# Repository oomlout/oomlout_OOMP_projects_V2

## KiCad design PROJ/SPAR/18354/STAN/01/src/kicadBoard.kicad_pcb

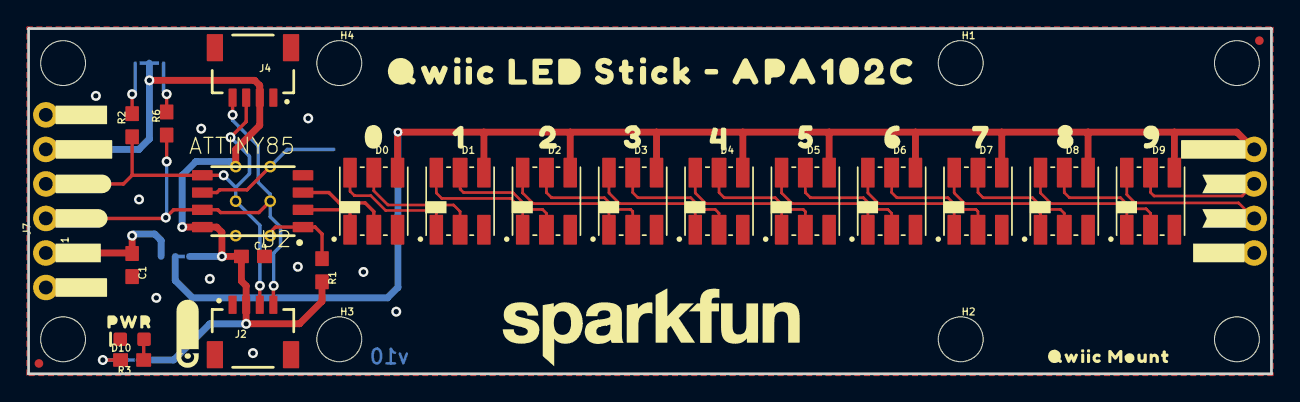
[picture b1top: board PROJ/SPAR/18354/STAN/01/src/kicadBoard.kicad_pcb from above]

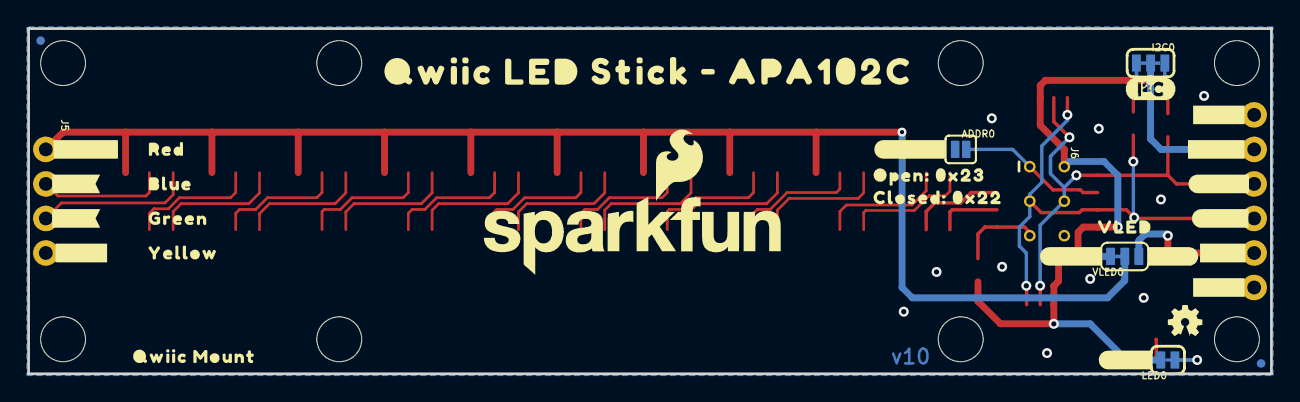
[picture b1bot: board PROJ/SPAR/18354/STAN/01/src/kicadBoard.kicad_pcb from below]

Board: 2 copper layers, 91.4 x 25.4 mm, 93 parts (35 on the bottom side), 34 nets.

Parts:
ADDR0: JUMPER-SMT_2_NO_SILK; SMT-JUMPER_2_NO_SILK
C1: 4.7uF; 0603
C4: 0.1uF; 0603
D0, D1, D2, D3, D4, D5, D6, D7, D8, D9: APA102-5050
D10: RED; LED-0603
FRAME1: FRAME-LETTER; CREATIVE_COMMONS
H1, H2, H3, H4: STAND-OFF
I2C0: JUMPER-SMT_3_2-NC_TRACE_SILK; SMT-JUMPER_3_2-NC_TRACE_SILK
J1: 1X02_NO_SILK
J2, J4: QWIIC_RA; JST04_1MM_RA
J5, J7: 1X04_NO_SILK
J6: AVR_SPI_PROG_3X2TESTPOINTS; 2X3_TEST_POINTS
JP1, JP2, JP5, JP6: FIDUCIALUFIDUCIAL; FIDUCIAL-MICRO
JP3, JP4, JP7, JP8: STAND-OFF
LED0: JUMPER-SMT_2_NC_TRACE_SILK; SMT-JUMPER_2_NC_TRACE_SILK
LOGO1: OSHW-LOGOMINI; OSHW-LOGO-MINI
LOGO2, LOGO5: SFE_LOGO_NAME.2_INCH; SFE_LOGO_NAME_.2
LOGO3: QWIIC_LOGO_5MM; QWIIC_5MM
LOGO4: SFE_LOGO_FLAME.2_INCH; SFE_LOGO_FLAME_.2
R1, R2, R6: 4.7k; 0603
R3: 1k; 0603
U2: ATTINY85
U$1, U$2, U$3, U$4, U$5, U$8: #GND#0
U$6: #CO#0
U$7: #DO#0
U$9, U$12: #VLED#0
U$10: #ADDR#0
U$11: (I_SUPER2_C)
U$14, U$17: #3#3V#0
U$15: #_DO#0
U$16: #_CO#0
U$18, U$19: #VIN#0
U$20: #SDA#0
U$21: #SDA_#0
U$22: #SCL#0
U$23: #SCL_#0
U$24: #LED#0
U$25: #3#3V#1
U$26: PWR0
U$28: VLED0
U$29: #VIN#4
U$30, U$47: QWIIC_MOUNT5
U$31: 00
U$32: 10
U$33: 20
U$34: 30
U$35: 40
U$36: 50
U$37: 60
U$38: 70
U$39: 80
U$40: 90
U$41: RED0
U$42: BLUE0
U$43: GREEN0
U$44: YELLOW0
U$45: OPEN#_0X230
U$46: CLOSED#_0X220
U$48, U$49: QWIIC_LED_STICK_#_APA102C0
VLED0: JUMPER-SMT_3_1-NC_TRACE_SILK; SMT-JUMPER_3_1-NC_TRACE_SILK

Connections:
3.3V: C4.1, I2C0.2, J2.2, J4.2, J6.2, J7.3, LED0.2, R1.2, U2.8, VLED0.3
ADDR/CIPO: ADDR0.2, J6.1, U2.6
CLK: D0.P2, U2.3
CO(10): D9.P5, J5.2
DO: D0.P1, U2.2
DO(10): D9.P6, J5.3
GND: ADDR0.1, C1.2, C4.2, D0.P3, D1.P3, D2.P3, D3.P3, D4.P3, D5.P3, D6.P3, D7.P3, D8.P3, D9.P3, D10.C, J1.2, J2.1, J4.1, J5.4, J6.6, J7.4, U2.4
unnamed: D10.A, R3.1
unnamed: LED0.1, R3.2
unnamed: I2C0.3, R2.2
unnamed: I2C0.1, R6.2
unnamed: D8.P6, D9.P1
unnamed: D8.P5, D9.P2
unnamed: D7.P5, D8.P2
unnamed: D7.P6, D8.P1
unnamed: D6.P5, D7.P2
unnamed: D6.P6, D7.P1
unnamed: D5.P5, D6.P2
unnamed: D5.P6, D6.P1
unnamed: D4.P5, D5.P2
unnamed: D4.P6, D5.P1
unnamed: D3.P5, D4.P2
unnamed: D3.P6, D4.P1
unnamed: D2.P6, D3.P1
unnamed: D2.P5, D3.P2
unnamed: D1.P6, D2.P1
unnamed: D1.P5, D2.P2
unnamed: D0.P5, D1.P2
unnamed: D0.P6, D1.P1
SCL/SCK: J2.4, J4.4, J6.3, J7.1, R6.1, U2.7
SDA/COPI: J2.3, J4.3, J6.4, J7.2, R2.1, U2.5
VIN: C1.1, J1.1, VLED0.1
VLED: D0.P4, D1.P4, D2.P4, D3.P4, D4.P4, D5.P4, D6.P4, D7.P4, D8.P4, D9.P4, J5.1, VLED0.2
~RST: J6.5, R1.1, U2.1

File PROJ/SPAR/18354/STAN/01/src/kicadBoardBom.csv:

"Id";"Designator";"Package";"Quantity";"Designation";"Supplier and ref";
1;"R2,R6,R1";"0603";3;"4.7k";;;
2;"U$3,U$1,U$5,U$4,U$8,U$2";"#GND#0";6;"";;;
3;"D3,D8,D4,D1,D2,D6,D0,D5,D9,D7";"APA102-5050";10;"APA102-5050";;;
4;"JP8,H3,JP3,H4,JP7,JP4,H1,H2";"STAND-OFF";8;"STAND-OFF";;;
5;"J1";"1X02_NO_SILK";1;"";;;
6;"U$35";"40";1;"";;;
7;"U$32";"10";1;"";;;
8;"JP6,JP2,JP1,JP5";"FIDUCIAL-MICRO";4;"FIDUCIALUFIDUCIAL";;;
9;"U$40";"90";1;"";;;
10;"U$38";"70";1;"";;;
11;"FRAME1";"CREATIVE_COMMONS";1;"FRAME-LETTER";;;
12;"U$37";"60";1;"";;;
13;"LOGO2,LOGO5";"SFE_LOGO_NAME_.2";2;"SFE_LOGO_NAME.2_INCH";;;
14;"D10";"LED-0603";1;"RED";;;
15;"J4,J2";"JST04_1MM_RA";2;"QWIIC_RA";;;
16;"U$9,U$12";"#VLED#0";2;"";;;
17;"U$36";"50";1;"";;;
18;"U$22";"#SCL#0";1;"";;;
19;"U$31";"00";1;"";;;
20;"U$48,U$49";"QWIIC_LED_STICK_#_APA102C0";2;"";;;
21;"U$26";"PWR0";1;"";;;
22;"U$7";"#DO#0";1;"";;;
23;"U$20";"#SDA#0";1;"";;;
24;"U$18,U$19";"#VIN#0";2;"";;;
25;"C1";"0603";1;"4.7uF";;;
26;"R3";"0603";1;"1k";;;
27;"U$6";"#CO#0";1;"";;;
28;"U$30,U$47";"QWIIC_MOUNT5";2;"";;;
29;"U2";"ATTINY85";1;"ATTINY85";;;
30;"U$34";"30";1;"";;;
31;"U$39";"80";1;"";;;
32;"LOGO3";"QWIIC_5MM";1;"QWIIC_LOGO_5MM";;;
33;"C4";"0603";1;"0.1uF";;;
34;"J7,J5";"1X04_NO_SILK";2;"";;;
35;"U$33";"20";1;"";;;
36;"U$14,U$17";"#3#3V#0";2;"";;;
37;"U$45";"OPEN#_0X230";1;"";;;
38;"U$46";"CLOSED#_0X220";1;"";;;
39;"U$10";"#ADDR#0";1;"";;;
40;"U$23";"#SCL_#0";1;"";;;
41;"U$15";"#_DO#0";1;"";;;
42;"LOGO4";"SFE_LOGO_FLAME_.2";1;"SFE_LOGO_FLAME.2_INCH";;;
43;"U$42";"BLUE0";1;"";;;
44;"U$21";"#SDA_#0";1;"";;;
45;"LOGO1";"OSHW-LOGO-MINI";1;"OSHW-LOGOMINI";;;
46;"U$41";"RED0";1;"";;;
47;"U$28";"VLED0";1;"";;;
48;"U$43";"GREEN0";1;"";;;
49;"U$16";"#_CO#0";1;"";;;
50;"U$25";"#3#3V#1";1;"";;;
51;"J6";"2X3_TEST_POINTS";1;"AVR_SPI_PROG_3X2TESTPOINTS";;;
52;"U$29";"#VIN#4";1;"";;;
53;"VLED0";"SMT-JUMPER_3_1-NC_TRACE_SILK";1;"JUMPER-SMT_3_1-NC_TRACE_SILK";;;
54;"LED0";"SMT-JUMPER_2_NC_TRACE_SILK";1;"JUMPER-SMT_2_NC_TRACE_SILK";;;
55;"U$44";"YELLOW0";1;"";;;
56;"U$11";"(I_SUPER2_C)";1;"";;;
57;"I2C0";"SMT-JUMPER_3_2-NC_TRACE_SILK";1;"JUMPER-SMT_3_2-NC_TRACE_SILK";;;
58;"ADDR0";"SMT-JUMPER_2_NO_SILK";1;"JUMPER-SMT_2_NO_SILK";;;
59;"U$24";"#LED#0";1;"";;;

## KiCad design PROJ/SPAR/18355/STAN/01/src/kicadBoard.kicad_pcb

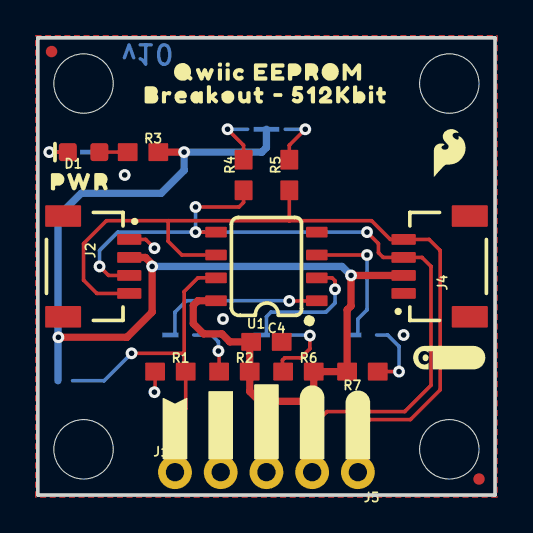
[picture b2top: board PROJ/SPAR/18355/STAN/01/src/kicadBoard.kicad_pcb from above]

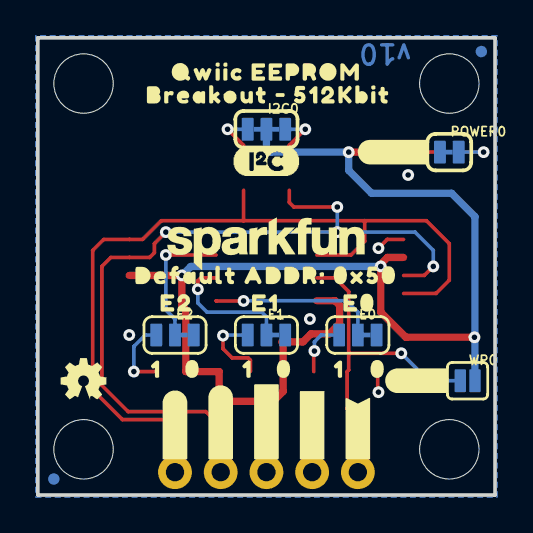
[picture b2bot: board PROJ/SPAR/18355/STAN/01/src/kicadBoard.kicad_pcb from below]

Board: 2 copper layers, 25.4 x 25.4 mm, 61 parts (30 on the bottom side), 15 nets.

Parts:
C4: 0.1uF; 0603
D1: RED; LED-0603
E0, E1, E2: JUMPER-SMT_3_1-NC_TRACE_SILK; SMT-JUMPER_3_1-NC_TRACE_SILK
FRAME1: FRAME-LETTER; CREATIVE_COMMONS
I2C0: JUMPER-SMT_3_2-NC_TRACE_SILK; SMT-JUMPER_3_2-NC_TRACE_SILK
J1: 1X01_NO_SILK
J2, J4: QWIIC_RA; JST04_1MM_RA
J5: 1X04_NO_SILK
JP1, JP2, JP5, JP6: FIDUCIALUFIDUCIAL; FIDUCIAL-MICRO
JP3, JP4, JP7, JP8: STAND-OFF
LOGO1: OSHW-LOGOMINI; OSHW-LOGO-MINI
LOGO2: SFE_LOGO_NAME.1_INCH; SFE_LOGO_NAME_.1
LOGO3: SFE_LOGO_FLAME.1_INCH; SFE_LOGO_FLAME_.1
LOGO4: QWIIC_LOGO_4MM; QWIIC_4MM
POWER0: JUMPER-SMT_2_NC_TRACE_SILK; SMT-JUMPER_2_NC_TRACE_SILK
R1, R2, R6, R7: 100k; 0603
R3: 1k; 0603
R4, R5: 4.7k; 0603
U1: CAT24C51; SO08
U$1, U$2: #WP#3
U$3: #WP#0
U$4: E00
U$5: E10
U$6: E20
U$7, U$8, U$9: 00
U$10, U$14: #GND#0
U$11: (I_SUPER2_C)
U$12: PWR0
U$13, U$21, U$22: 10
U$15, U$16: #3#3V#0
U$17, U$29: #SDA#0
U$18: #LED#2
U$19, U$20: QWIIC_EEPROM0
U$23, U$24: BREAKOUT_#_512KBIT0
U$25: DEFAULT_ADDR#_0X500
U$30, U$31: #SCL#0
WP0: JUMPER-SMT_2_NO_SILK; SMT-JUMPER_2_NO_SILK

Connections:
3.3V: C4.1, I2C0.2, J2.2, J4.2, J5.3, R2.2, R3.2, R6.2, R7.2, U1.8, WP0.2
GND: C4.2, E0.3, E1.3, E2.3, J2.1, J4.1, J5.4, POWER0.1, R1.1, U1.4
unnamed: I2C0.1, R5.2
unnamed: I2C0.3, R4.2
unnamed: D1.A, R3.1
unnamed: E2.2, U1.3
unnamed: E1.2, U1.2
unnamed: E0.2, U1.1
unnamed: E0.1, R2.1
unnamed: E2.1, R7.1
unnamed: E1.1, R6.1
unnamed: D1.C, POWER0.2
SCL: J2.4, J4.4, J5.1, R5.1, U1.6
SDA: J2.3, J4.3, J5.2, R4.1, U1.5
WP: J1.1, R1.2, U1.7, WP0.1

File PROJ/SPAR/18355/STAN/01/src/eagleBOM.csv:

"Part";"Value";"Device";"Package";"Description";"DESIGNER";"PROD_ID";"REV";"VALUE";
"C4";"0.1uF";"0.1UF-0603-25V-(+80/-20%)";"0603";"0.1µF ceramic capacitors";"";"CAP-00810";"";"0.1uF";
"D1";"RED";"LED-RED0603";"LED-0603";"Red SMD LED";"";"DIO-00819";"";"RED";
"E0";"JUMPER-SMT_3_1-NC_TRACE_SILK";"JUMPER-SMT_3_1-NC_TRACE_SILK";"SMT-JUMPER_3_1-NC_TRACE_SILK";"Normally closed trace jumper (1 of 2 connections)";"";"";"";"";
"E1";"JUMPER-SMT_3_1-NC_TRACE_SILK";"JUMPER-SMT_3_1-NC_TRACE_SILK";"SMT-JUMPER_3_1-NC_TRACE_SILK";"Normally closed trace jumper (1 of 2 connections)";"";"";"";"";
"E2";"JUMPER-SMT_3_1-NC_TRACE_SILK";"JUMPER-SMT_3_1-NC_TRACE_SILK";"SMT-JUMPER_3_1-NC_TRACE_SILK";"Normally closed trace jumper (1 of 2 connections)";"";"";"";"";
"FRAME1";"FRAME-LETTER";"FRAME-LETTER";"CREATIVE_COMMONS";"Schematic Frame - Letter";"";"";"";"";
"I2C";"JUMPER-SMT_3_2-NC_TRACE_SILK";"JUMPER-SMT_3_2-NC_TRACE_SILK";"SMT-JUMPER_3_2-NC_TRACE_SILK";"Normally closed trace jumper (2 of 2 connections)";"";"";"";"";
"J1";"";"CONN_01PTH_NO_SILK_YES_STOP";"1X01_NO_SILK";"Single connection point. Often used as Generic Header-pin footprint for 0.1 inch spaced/style header connections";"";"";"";"";
"J2";"QWIIC_RA";"QWIIC_CONNECTORJS-1MM";"JST04_1MM_RA";"SparkFun I2C Standard Qwiic Connector";"";"CONN-13694";"";"QWIIC_RIGHT_ANGLE";
"J4";"QWIIC_RA";"QWIIC_CONNECTORJS-1MM";"JST04_1MM_RA";"SparkFun I2C Standard Qwiic Connector";"";"CONN-13694";"";"QWIIC_RIGHT_ANGLE";
"J5";"";"CONN_041X04_NO_SILK_NO_POP";"1X04_NO_SILK";"Multi connection point. Often used as Generic Header-pin footprint for 0.1 inch spaced/style header connections";"";"";"";"";
"JP1";"FIDUCIALUFIDUCIAL";"FIDUCIALUFIDUCIAL";"FIDUCIAL-MICRO";"Fiducial Alignment Points";"";"";"";"";
"JP2";"FIDUCIALUFIDUCIAL";"FIDUCIALUFIDUCIAL";"FIDUCIAL-MICRO";"Fiducial Alignment Points";"";"";"";"";
"JP3";"STAND-OFF";"STAND-OFF";"STAND-OFF";"Stand Off";"";"";"";"";
"JP4";"STAND-OFF";"STAND-OFF";"STAND-OFF";"Stand Off";"";"";"";"";
"JP5";"FIDUCIALUFIDUCIAL";"FIDUCIALUFIDUCIAL";"FIDUCIAL-MICRO";"Fiducial Alignment Points";"";"";"";"";
"JP6";"FIDUCIALUFIDUCIAL";"FIDUCIALUFIDUCIAL";"FIDUCIAL-MICRO";"Fiducial Alignment Points";"";"";"";"";
"JP7";"STAND-OFF";"STAND-OFF";"STAND-OFF";"Stand Off";"";"";"";"";
"JP8";"STAND-OFF";"STAND-OFF";"STAND-OFF";"Stand Off";"";"";"";"";
"LOGO1";"OSHW-LOGOMINI";"OSHW-LOGOMINI";"OSHW-LOGO-MINI";"Open-Source Hardware (OSHW) Logo";"";"";"";"";
"LOGO2";"SFE_LOGO_NAME.1_INCH";"SFE_LOGO_NAME.1_INCH";"SFE_LOGO_NAME_.1";"SparkFun Font Logo";"";"";"";"";
"LOGO3";"SFE_LOGO_FLAME.1_INCH";"SFE_LOGO_FLAME.1_INCH";"SFE_LOGO_FLAME_.1";"SparkFun Flame Logo";"";"";"";"";
"LOGO4";"QWIIC_LOGO_4MM";"QWIIC_LOGO_4MM";"QWIIC_4MM";"Qwiic Logos for placement on schematic and PCB. The 5.5mm silk logo is best for placing next to Qwiic connector.";"";"";"";"";
"POWER";"JUMPER-SMT_2_NC_TRACE_SILK";"JUMPER-SMT_2_NC_TRACE_SILK";"SMT-JUMPER_2_NC_TRACE_SILK";"Normally closed trace jumper";"";"";"";"";
"R1";"100k";"100KOHM-0603-1/10W-1%";"0603";"100kΩ resistor";"";"RES-07828";"";"100k";
"R2";"100k";"100KOHM-0603-1/10W-1%";"0603";"100kΩ resistor";"";"RES-07828";"";"100k";
"R3";"1k";"1KOHM-0603-1/10W-1%";"0603";"1kΩ resistor";"";"RES-07856";"";"1k";
"R4";"4.7k";"4.7KOHM-0603-1/10W-1%";"0603";"4.7kΩ resistor";"";"RES-07857";"";"4.7k";
"R5";"4.7k";"4.7KOHM-0603-1/10W-1%";"0603";"4.7kΩ resistor";"";"RES-07857";"";"4.7k";
"R6";"100k";"100KOHM-0603-1/10W-1%";"0603";"100kΩ resistor";"";"RES-07828";"";"100k";
"R7";"100k";"100KOHM-0603-1/10W-1%";"0603";"100kΩ resistor";"";"RES-07828";"";"100k";
"U1";"CAT24C51";"RM24C512C";"SO08";"";"";"IC-14645";"";"";
"WP";"JUMPER-SMT_2_NO_SILK";"JUMPER-SMT_2_NO_SILK";"SMT-JUMPER_2_NO_SILK";"Normally open jumper";"";"";"";"";

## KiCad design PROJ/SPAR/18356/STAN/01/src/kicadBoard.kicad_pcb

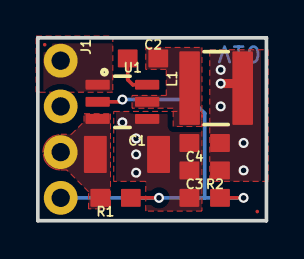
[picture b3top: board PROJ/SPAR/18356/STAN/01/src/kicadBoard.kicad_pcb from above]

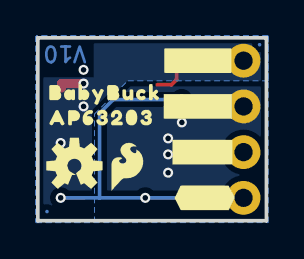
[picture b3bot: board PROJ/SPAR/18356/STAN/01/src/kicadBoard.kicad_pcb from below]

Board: 2 copper layers, 12.7 x 10.2 mm, 23 parts (10 on the bottom side), 6 nets.

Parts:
C1: 10uF; 1210
C2: 0.1uF; 0603
C3, C4: 22uF; 0603
FD1, FD2, FD3, FD4: FIDUCIAL0.2MM; FIDUCIAL-0.2MM
FRAME1: FRAME-LETTER; CREATIVE_COMMONS
J1: 1X04_NO_SILK
L1: 4.7μH; INDUCTOR_4X4MM
LOGO1: SFE_LOGO_FLAME.1_INCH; SFE_LOGO_FLAME_.1
LOGO2: OSHW-LOGOS; OSHW-LOGO-S
LOGO3: SPECIAL_INSTRUCTIONS-ORDERING; ORDERING_INSTRUCTIONS
R1, R2: 100k; 0603
U1: AP63203; SOT23-6
U$1: #3V3#0
U$2: #GND#0
U$3: #VIN#0
U$4: #EN#0
U$7: AP632030
U$8: BABYBUCK0

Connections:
3.3V: C3.1, C4.1, J1.1, L1.P$2, U1.1
EN: J1.4, R1.1, R2.2, U1.2
GND: C1.2, C3.2, C4.2, J1.2, R2.1, U1.4
unnamed: C2.1, U1.6
unnamed: C2.2, L1.P$1, U1.5
VIN: C1.1, J1.3, R1.2, U1.3

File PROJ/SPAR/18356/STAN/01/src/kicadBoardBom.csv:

"Id";"Designator";"Package";"Quantity";"Designation";"Supplier and ref";
1;"LOGO3";"ORDERING_INSTRUCTIONS";1;"SPECIAL_INSTRUCTIONS-ORDERING";;;
2;"FD1,FD3,FD4,FD2";"FIDUCIAL-0.2MM";4;"FIDUCIAL0.2MM";;;
3;"L1";"INDUCTOR_4X4MM";1;"4.7μH";;;
4;"R1,R2";"0603";2;"100k";;;
5;"C3,C4";"0603";2;"22uF";;;
6;"U1";"SOT23-6";1;"AP63203";;;
7;"C1";"1210";1;"10uF";;;
8;"C2";"0603";1;"0.1uF";;;
9;"J1";"1X04_NO_SILK";1;"";;;
10;"FRAME1";"CREATIVE_COMMONS";1;"FRAME-LETTER";;;
11;"U$4";"#EN#0";1;"";;;
12;"LOGO1";"SFE_LOGO_FLAME_.1";1;"SFE_LOGO_FLAME.1_INCH";;;
13;"U$2";"#GND#0";1;"";;;
14;"LOGO2";"OSHW-LOGO-S";1;"OSHW-LOGOS";;;
15;"U$8";"BABYBUCK0";1;"";;;
16;"U$1";"#3V3#0";1;"";;;
17;"U$7";"AP632030";1;"";;;
18;"U$3";"#VIN#0";1;"";;;

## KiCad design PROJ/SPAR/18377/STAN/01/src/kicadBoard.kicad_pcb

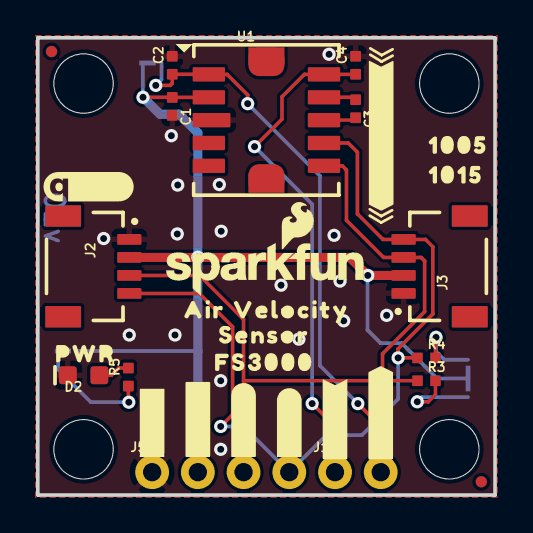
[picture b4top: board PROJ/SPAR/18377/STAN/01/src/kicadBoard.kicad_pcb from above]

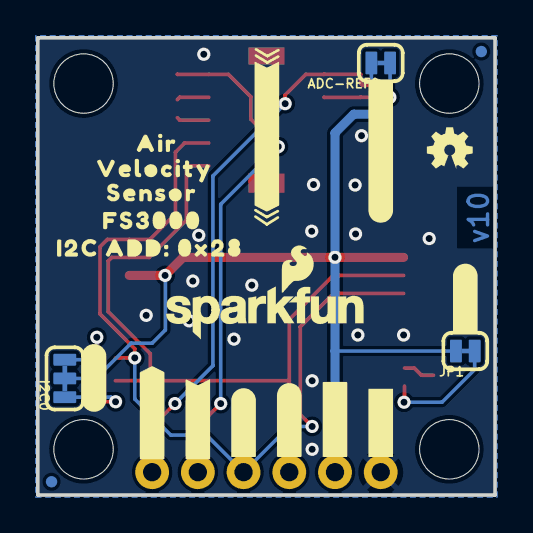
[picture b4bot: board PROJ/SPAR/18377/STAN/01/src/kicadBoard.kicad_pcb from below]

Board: 2 copper layers, 25.4 x 25.4 mm, 58 parts (22 on the bottom side), 12 nets.

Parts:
ADC-REF0: SMT-JUMPER_2_NC_TRACE_SILK
C1, C2, C3: 0.1uF; 0402-TIGHT
C4: 1.0uF; 0402-TIGHT
D2: RED; LED-0603
FRAME1: FRAME-LETTER; CREATIVE_COMMONS
I2C0: SMT-JUMPER_3_2-NC_TRACE_SILK
J1: 1X02_NO_SILK
J2, J3: QWIIC_RA; JST04_1MM_RA
J5: 1X04_NO_SILK
JP1: LED; SMT-JUMPER_2_NC_TRACE_SILK
JP2, JP5, JP6, JP11: FIDUCIALUFIDUCIAL; FIDUCIAL-MICRO
JP3, JP4, JP7, JP8: STAND-OFF
LOGO1: OSHW-LOGOMINI; OSHW-LOGO-MINI
LOGO3, LOGO5: SFE_LOGO_NAME_FLAME.1_INCH; SFE_LOGO_NAME_FLAME_.1
LOGO4: QWIIC_LOGO_5MM; QWIIC_5MM
R3, R4: 2.2k; 0402-TIGHT
R5: 1k; 0402-TIGHT
U1: FS3000
U$3, U$11: #SCL#0
U$4, U$9: #SDA#0
U$5, U$6: #GND#0
U$7, U$8: #3#3V#0
U$10, U$13: #ADCR#4
U$12: 10050
U$14, U$17: FS30001
U$15: #ADC#REF#0
U$16, U$20: VELOCITY30003
U$18, U$21: AIR30004
U$19, U$22: SENSOR30005
U$23, U$26: #AIRFLOW#0
U$24: #LED#0
U$25: PWR0
U$27: #I2C#0
U$28: I2C_ADD#_0X280
U$29: 10150
U$30, U$31: #VCM#3

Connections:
3.3V: ADC-REF0.1, C1.1, I2C0.2, J2.2, J3.2, J5.2, JP1.2, U1.2
ADC-REF: ADC-REF0.2, C2.1, J1.2, U1.1
GND: C1.2, C2.2, C4.2, D2.C, J2.1, J3.1, J5.1, U1.3
unnamed: I2C0.1, R3.2
unnamed: I2C0.3, R4.2
unnamed: C3.1, U1.9
unnamed: C3.2, U1.8
unnamed: D2.A, R5.2
unnamed: JP1.1, R5.1
SCL: J2.4, J3.4, J5.4, R4.1, U1.7
SDA: J2.3, J3.3, J5.3, R3.1, U1.6
VCM: C4.1, J1.1, U1.10

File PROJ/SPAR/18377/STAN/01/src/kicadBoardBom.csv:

"Id";"Designator";"Package";"Quantity";"Designation";"Supplier and ref";
1;"LOGO4";"QWIIC_5MM";1;"QWIIC_LOGO_5MM";;;
2;"U$10,U$13";"#ADCR#4";2;"";;;
3;"JP4,JP3,JP8,JP7";"STAND-OFF";4;"STAND-OFF";;;
4;"LOGO5,LOGO3";"SFE_LOGO_NAME_FLAME_.1";2;"SFE_LOGO_NAME_FLAME.1_INCH";;;
5;"U$19,U$22";"SENSOR30005";2;"";;;
6;"U$30,U$31";"#VCM#3";2;"";;;
7;"FRAME1";"CREATIVE_COMMONS";1;"FRAME-LETTER";;;
8;"JP2,JP6,JP11,JP5";"FIDUCIAL-MICRO";4;"FIDUCIALUFIDUCIAL";;;
9;"R4,R3";"0402-TIGHT";2;"2.2k";;;
10;"U$23,U$26";"#AIRFLOW#0";2;"";;;
11;"U1";"FS3000";1;"FS3000";;;
12;"C1,C2,C3";"0402-TIGHT";3;"0.1uF";;;
13;"U$18,U$21";"AIR30004";2;"";;;
14;"D2";"LED-0603";1;"RED";;;
15;"U$7,U$8";"#3#3V#0";2;"";;;
16;"U$11,U$3";"#SCL#0";2;"";;;
17;"J3,J2";"JST04_1MM_RA";2;"QWIIC_RA";;;
18;"U$16,U$20";"VELOCITY30003";2;"";;;
19;"R5";"0402-TIGHT";1;"1k";;;
20;"U$12";"10050";1;"";;;
21;"U$25";"PWR0";1;"";;;
22;"U$14,U$17";"FS30001";2;"";;;
23;"U$29";"10150";1;"";;;
24;"C4";"0402-TIGHT";1;"1.0uF";;;
25;"J1";"1X02_NO_SILK";1;"";;;
26;"J5";"1X04_NO_SILK";1;"";;;
27;"U$9,U$4";"#SDA#0";2;"";;;
28;"U$5,U$6";"#GND#0";2;"";;;
29;"ADC-REF0";"SMT-JUMPER_2_NC_TRACE_SILK";1;"";;;
30;"U$15";"#ADC#REF#0";1;"";;;
31;"U$28";"I2C_ADD#_0X280";1;"";;;
32;"U$27";"#I2C#0";1;"";;;
33;"JP1";"SMT-JUMPER_2_NC_TRACE_SILK";1;"LED";;;
34;"LOGO1";"OSHW-LOGO-MINI";1;"OSHW-LOGOMINI";;;
35;"U$24";"#LED#0";1;"";;;
36;"I2C0";"SMT-JUMPER_3_2-NC_TRACE_SILK";1;"";;;

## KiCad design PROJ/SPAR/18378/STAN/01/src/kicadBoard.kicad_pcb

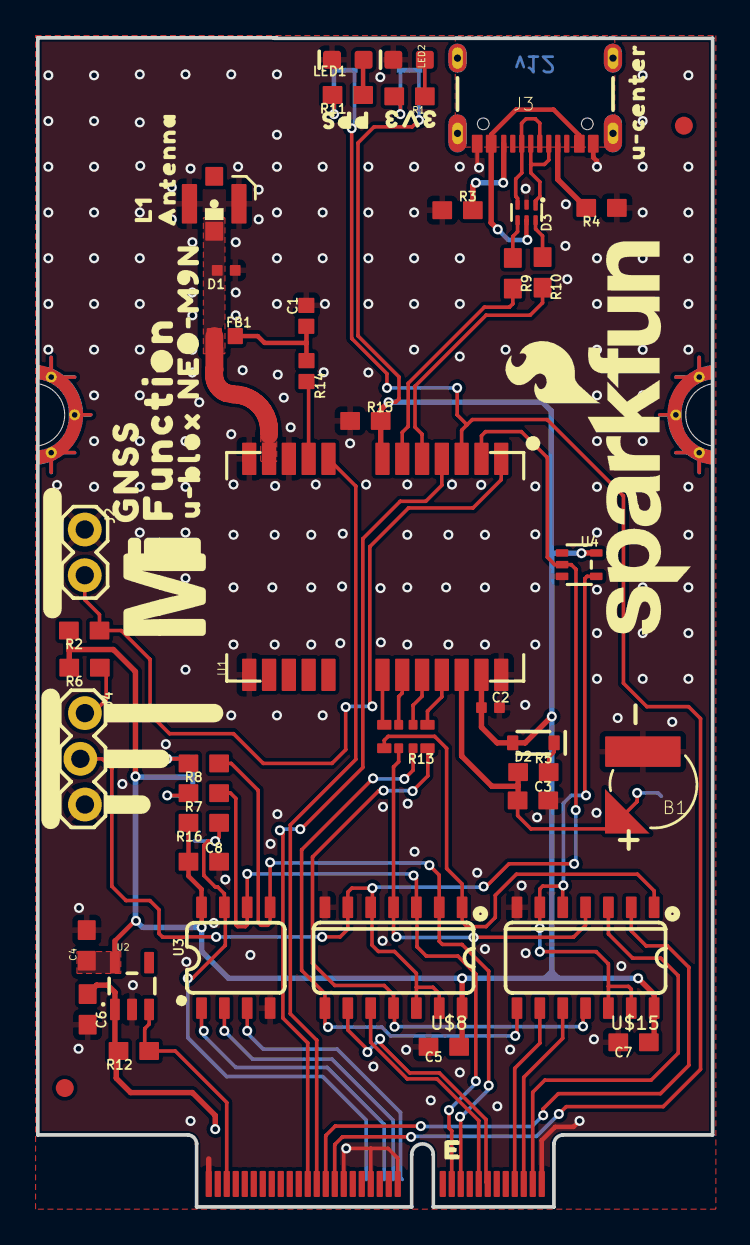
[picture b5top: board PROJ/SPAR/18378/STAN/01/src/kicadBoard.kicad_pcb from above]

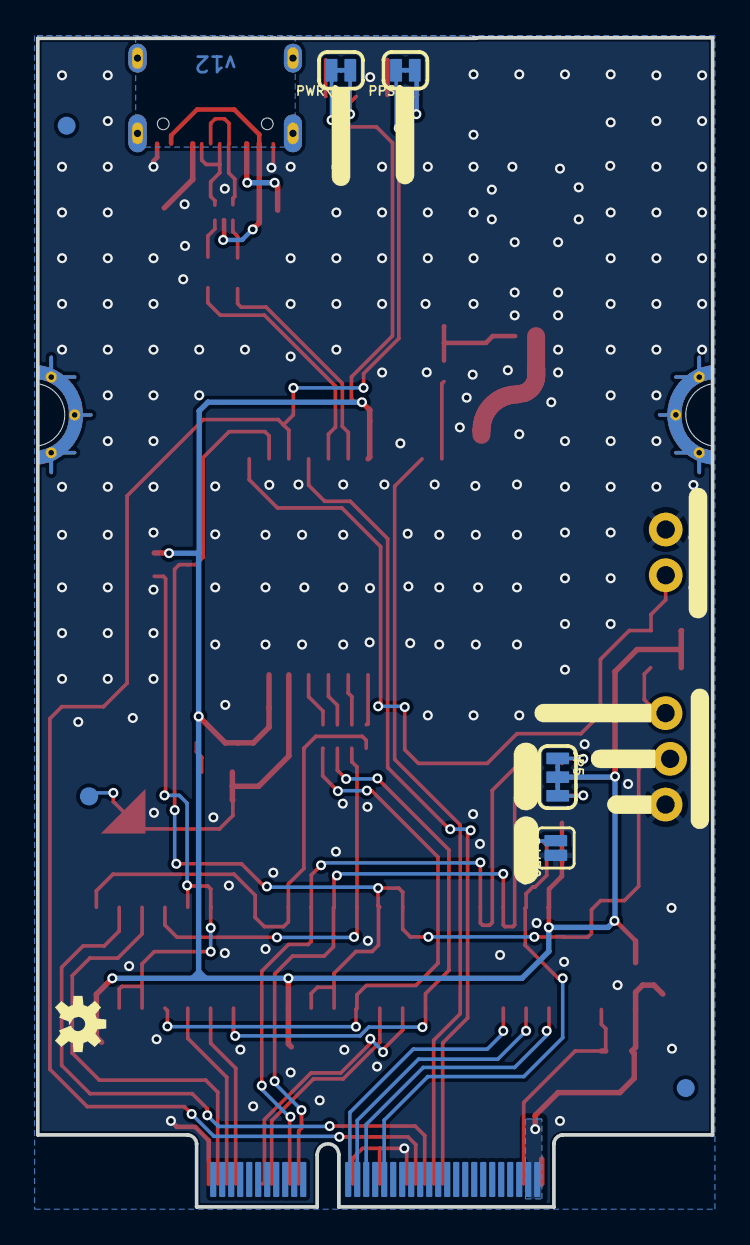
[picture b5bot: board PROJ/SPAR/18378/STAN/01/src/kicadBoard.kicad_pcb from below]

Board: 2 copper layers, 37.5 x 64.9 mm, 79 parts (17 on the bottom side), 52 nets.

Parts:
B1: 6.8MM_COIN_CELL; MS421R_IV03E
C1: 47pF; 0402
C2: 0.1uF; 0402-TIGHT
C3, C4, C6: 1.0uF; 0603
C5, C7, C8: 0.1uF; 0603
D1: PESD0402-0402T; 0402-TIGHT
D2: 0.5A/40V/420mV; SOD-323
D3: PRTR5V0U2F; SOT886
E1: U.FL
FB1: 120Ω; 0402
FD1, FD2, FD3, FD4: FIDUCIAL1X2; FIDUCIAL-1X2
FRAME2: FRAME-LEDGER; CREATIVE_COMMONS
J1: MICROMOD_FUNCTION_STANDARD; M.2-CARD-E-22_FUNCTION_STANDARD
J2: 1X02
J3: USB-C-16P-2LAYER-PADS
J4: Bus Selection; 1X03_LOCK
JP5: JUMPER-SMT_3_2-NC_TRACE_SILK; SMT-JUMPER_3_2-NC_TRACE_SILK
LED1: BLUE; LED-0603
LED2: RED; LED-0603
LOGO1: SPECIAL_INSTRUCTIONS-ORDERING; ORDERING_INSTRUCTIONS
LOGO2: SFE_LOGO_NAME_FLAME.2_INCH; SFE_LOGO_NAME_FLAME_.2
LOGO3: OSHW-LOGOS; OSHW-LOGO-S
PPS0: JUMPER-SMT_2_NC_TRACE_SILK; SMT-JUMPER_2_NC_TRACE_SILK
PWR\0: JUMPER-SMT_2_NC_TRACE_SILK; SMT-JUMPER_2_NC_TRACE_SILK
R1, R11: 1k; 0603
R2, R6, R16: 10k; 0603
R3, R4: 5.1k; 0603
R5: 3.3k; 0603
R7, R8: 2.2k; 0603
R9, R10: 27; 0603
R12, R15: 100k; 0603
R13: 33; 1206_RA
R14: 33; 0402
TP1: TEST-POINT3X4; PAD.03X.04
U1: U-BLOX_NEO-M9N; NEO-M9N_M8T_M8U_D9S
U2: 3.3V; SOT23-5
U3: EEPROM; SO08
U4: 74HC1G04; SOT353
U$1: 3V313
U$2: PPS13
U$3: FUNCTION521
U$4, U$23: ##SAFEBOOT##882188213
U$5: U#BLOX11
U$6: NEO#M9N12
U$7: ANTENNA14
U$8, U$15: 74LVC4066D_QUAD_BILATERAL_SWITCH; SO14
U$9: U#CENTER15
U$10: #I2C#18
U$11: MICROMOD_MI_LOGO_1
U$12: #3V3_LED#403132222514
U$13: #PPS_LED#403132222514
U$14: L1321542
U$16, U$24: #SPI#40313521
U$17, U$26: #SERIAL#I2C#40313523
U$18, U$22: #BUS_SELECT#509
U$19, U$25: #DSEL#40313522
U$20: #WP#13215403132222564
U$21: GNSS2222502
WP0: JUMPER-SMT_2_NO_SILK; SMT-JUMPER_2_NO_SILK

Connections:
3.3V: C2.1, C4.1, C5.1, C7.1, C8.1, D2.A, JP5.2, PWR\0.2, R2.2, R6.2, R15.2, R16.2, U1.7, U1.23, U2.5, U3.8, U4.5, U$8.14, U$15.14
A0: J1.36, U3.1
A1: J1.34, U3.2
A2: J1.32, U3.3
D+: D3.4, R9.1
D-: D3.6, R10.1
D_SEL: J4.2, U1.2, U4.2, U$8.5, U$8.6, U$8.12, U$8.13
EN: J1.71, R12.1, U2.3
GND: B1.-, C1.2, C2.2, C3.2, C4.2, C5.2, C6.2, C7.2, C8.2, D1.1, D3.2, E1.1, E1.2, J1.1, J1.33, J1.39, J1.45, J1.75, J1.GND1, J1.GND2, J1.GND3, J1.GND4, J1.GND5, J1.GND6, J2.1, J3.GND, J3.GND2, J4.3, LED1.C, LED2.C, R3.1, R4.1, R15.1, U1.10, U1.12, U1.13, U1.24, U2.2, U3.4, U4.3, U$8.7, U$15.7, WP0.1
GPS_ANT1: D1.2, E1.FEED, FB1.1, U1.11
INT: J1.53, U1.4
INV_D_SEL: U4.4, U$15.5, U$15.6, U$15.12, U$15.13
unnamed: PWR\0.1, R1.2
unnamed: LED1.A, R11.1
unnamed: C1.1, FB1.2, R14.1
unnamed: PPS0.1, R11.2
unnamed: JP5.1, R8.2
unnamed: D2.C, R5.2
unnamed: J3.A5, R4.2
unnamed: JP5.3, R7.2
unnamed: J3.B5, R3.2
unnamed: LED2.A, R1.1
unnamed: R9.2, U1.6
unnamed: R10.2, U1.5
unnamed: J4.1, R6.1
PICO: J1.5, U$15.10
POCI: J1.7, U$15.9
PPS: J1.47, PPS0.2, U1.3
RXI: J1.15, U$8.10
RXI/PICO: R13.P8, U$8.11, U$15.11
RXLV: R13.P1, U1.21
SCK: J1.3, U$15.3
SCL: J1.21, R7.1, U3.6, U$8.3
SCL/SCK: R13.P6, U$8.4, U$15.4
SCL_LV: R13.P3, U1.19
SDA: J1.19, R8.1, U3.5, U$8.2
SDA/SPI_~CS: R13.P5, U$8.1, U$15.1
SDA_LV: R13.P4, U1.18
SHLD: J3.SHLD1, J3.SHLD2, J3.SHLD3, J3.SHLD4
SPI_~CS: J1.49, U$15.2
TXLV: R13.P2, U1.20
TXO: J1.13, U$8.9
TXO/POCI: R13.P7, U$8.8, U$15.8
USB_D+: D3.3, J3.A6, J3.B6
USB_D-: D3.1, J3.A7, J3.B7
VCC: C6.1, J1.72, J1.74, R12.2, U2.1
VCC_RF: R14.2, U1.9
V_BATT: B1.+, C3.1, R5.1, TP1.1, U1.22
V_USB: D3.5, J3.VBUS1, J3.VBUS2
WP: J1.40, R16.1, U3.7, WP0.2
~RESET: J1.51, U1.8
~SAFE: J2.2, R2.1, U1.1

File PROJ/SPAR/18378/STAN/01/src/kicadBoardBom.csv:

"Id";"Designator";"Package";"Quantity";"Designation";"Supplier and ref";
1;"R11,R1";"0603";2;"1k";;;
2;"R12,R15";"0603";2;"100k";;;
3;"C3,C4,C6";"0603";3;"1.0uF";;;
4;"U$6";"NEO#M9N12";1;"";;;
5;"C7,C8,C5";"0603";3;"0.1uF";;;
6;"U$4,U$23";"##SAFEBOOT##882188213";2;"";;;
7;"U$3";"FUNCTION521";1;"";;;
8;"U$17,U$26";"#SERIAL#I2C#40313523";2;"";;;
9;"C2";"0402-TIGHT";1;"0.1uF";;;
10;"R3,R4";"0603";2;"5.1k";;;
11;"J2";"1X02";1;"";;;
12;"U$2";"PPS13";1;"";;;
13;"J3";"USB-C-16P-2LAYER-PADS";1;"";;;
14;"U$9";"U#CENTER15";1;"";;;
15;"U4";"SOT353";1;"74HC1G04";;;
16;"D1";"0402-TIGHT";1;"PESD0402-0402T";;;
17;"FD2,FD4,FD3,FD1";"FIDUCIAL-1X2";4;"FIDUCIAL1X2";;;
18;"R5";"0603";1;"3.3k";;;
19;"R9,R10";"0603";2;"27";;;
20;"R16,R2,R6";"0603";3;"10k";;;
21;"LED2";"LED-0603";1;"RED";;;
22;"C1";"0402";1;"47pF";;;
23;"R14";"0402";1;"33";;;
24;"D2";"SOD-323";1;"0.5A/40V/420mV";;;
25;"U3";"SO08";1;"EEPROM";;;
26;"U$19,U$25";"#DSEL#40313522";2;"";;;
27;"U1";"NEO-M9N_M8T_M8U_D9S";1;"U-BLOX_NEO-M9N";;;
28;"R7,R8";"0603";2;"2.2k";;;
29;"U$5";"U#BLOX11";1;"";;;
30;"R13";"1206_RA";1;"33";;;
31;"U$15,U$8";"SO14";2;"74LVC4066D_QUAD_BILATERAL_SWITCH";;;
32;"LOGO1";"ORDERING_INSTRUCTIONS";1;"SPECIAL_INSTRUCTIONS-ORDERING";;;
33;"U$11";"MICROMOD_MI_LOGO_1";1;"";;;
34;"U$1";"3V313";1;"";;;
35;"U$7";"ANTENNA14";1;"";;;
36;"U$21";"GNSS2222502";1;"";;;
37;"LOGO2";"SFE_LOGO_NAME_FLAME_.2";1;"SFE_LOGO_NAME_FLAME.2_INCH";;;
38;"FRAME2";"CREATIVE_COMMONS";1;"FRAME-LEDGER";;;
39;"E1";"U.FL";1;"U.FL";;;
40;"FB1";"0402";1;"120Ω";;;
41;"LED1";"LED-0603";1;"BLUE";;;
42;"B1";"MS421R_IV03E";1;"6.8MM_COIN_CELL";;;
43;"U$14";"L1321542";1;"";;;
44;"D3";"SOT886";1;"PRTR5V0U2F";;;
45;"J4";"1X03_LOCK";1;"Bus Selection";;;
46;"J1";"M.2-CARD-E-22_FUNCTION_STANDARD";1;"MICROMOD_FUNCTION_STANDARD";;;
47;"U$18,U$22";"#BUS_SELECT#509";2;"";;;
48;"U$16,U$24";"#SPI#40313521";2;"";;;
49;"U2";"SOT23-5";1;"3.3V";;;
50;"U$20";"#WP#13215403132222564";1;"";;;
51;"JP5";"SMT-JUMPER_3_2-NC_TRACE_SILK";1;"JUMPER-SMT_3_2-NC_TRACE_SILK";;;
52;"LOGO3";"OSHW-LOGO-S";1;"OSHW-LOGOS";;;
53;"U$13";"#PPS_LED#403132222514";1;"";;;
54;"PWR\0,PPS0";"SMT-JUMPER_2_NC_TRACE_SILK";2;"JUMPER-SMT_2_NC_TRACE_SILK";;;
55;"WP0";"SMT-JUMPER_2_NO_SILK";1;"JUMPER-SMT_2_NO_SILK";;;
56;"TP1";"PAD.03X.04";1;"TEST-POINT3X4";;;
57;"U$10";"#I2C#18";1;"";;;
58;"U$12";"#3V3_LED#403132222514";1;"";;;

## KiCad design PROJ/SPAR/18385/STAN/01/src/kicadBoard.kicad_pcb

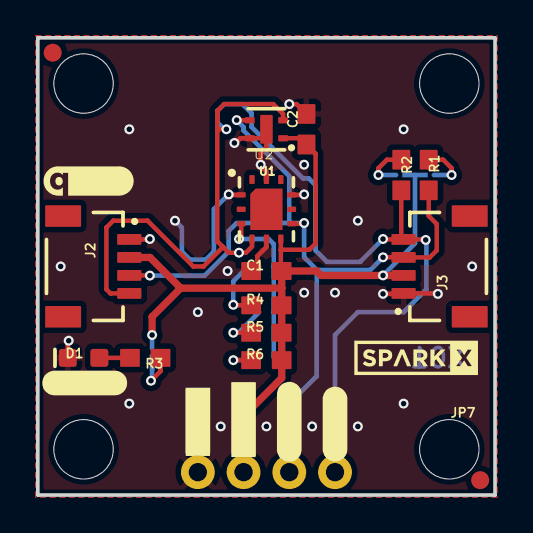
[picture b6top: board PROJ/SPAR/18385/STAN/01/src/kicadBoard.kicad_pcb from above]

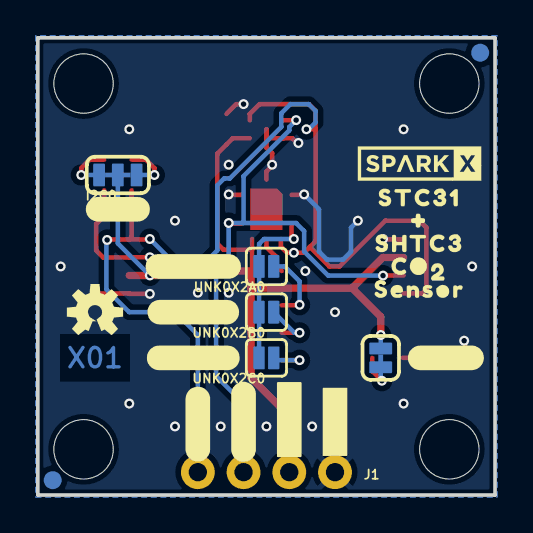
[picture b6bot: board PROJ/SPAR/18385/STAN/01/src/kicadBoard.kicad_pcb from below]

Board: 4 copper layers, 25.4 x 25.4 mm, 53 parts (25 on the bottom side), 12 nets.

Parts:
C1, C2: 0.1uF; 0603
D1: RED; LED-0603
FRAME1: FRAME-LETTER; CREATIVE_COMMONS
I2C0: JUMPER-SMT_3_2-NC_TRACE_SILK; SMT-JUMPER_3_2-NC_TRACE_SILK
J1: 1X04_NO_SILK
J2, J3: QWIIC_RIGHT_ANGLE; JST04_1MM_RA
JP1, JP2, JP5, JP6: FIDUCIAL1X2; FIDUCIAL-1X2
JP3, JP4, JP7, JP8: STAND-OFF
LED0: JUMPER-SMT_2_NC_TRACE_SILK; SMT-JUMPER_2_NC_TRACE_SILK
LOGO1: SPECIAL_INSTRUCTIONS-ORDERING; ORDERING_INSTRUCTIONS
LOGO2: QWIIC_LOGO_5MM; QWIIC_5MM
LOGO5: OSHW-LOGOS; OSHW-LOGO-S
R1, R2: 4.7k; 0603
R3, R6: 1k; 0603
R4: 10k; 0603
R5: 3.3k; 0603
U1: STC31
U2: SHTC3
U$1, U$33: #GND#0
U$2, U$34: #3#3V#0
U$3, U$35: #SDA#0
U$4, U$36: #SCL#0
U$5: #LED#0
U$6: #0X2A#0
U$7: #0X2B#0
U$8: #0X2C#0
U$9: #I�C#0
U$10, U$18: SPARKX-LOGO3; SPARKX-SMALL
U$11: STC310
U$12: #0
U$13: SHTC30
U$14: CO0
U$15: 20
U$16: SENSOR0
U$32: #PWR#0
UNK0X2A0, UNK0X2B0, UNK0X2C0: JUMPER-SMT_2_NO_SILK; SMT-JUMPER_2_NO_SILK

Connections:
3.3V: C1.1, C2.1, I2C0.2, J1.2, J2.2, J3.2, LED0.2, R4.1, R5.1, R6.1, U1.6, U2.1
ADDR: U1.3, UNK0X2A0.2, UNK0X2B0.2, UNK0X2C0.2
GND: C1.2, C2.2, D1.C, J1.1, J2.1, J3.1, U1.1, U1.5, U1.9, U1.11, U1.DIEPAD, U2.4, U2.5
unnamed: LED0.1, R3.2
unnamed: I2C0.3, R1.2
unnamed: D1.A, R3.1
unnamed: I2C0.1, R2.2
unnamed: R4.2, UNK0X2A0.1
unnamed: R5.2, UNK0X2B0.1
unnamed: R6.2, UNK0X2C0.1
SCL: J1.4, J2.4, J3.4, R2.1, U1.4, U2.2
SDA: J1.3, J2.3, J3.3, R1.1, U1.7, U2.3

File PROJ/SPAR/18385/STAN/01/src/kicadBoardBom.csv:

"Id";"Designator";"Package";"Quantity";"Designation";"Supplier and ref";
1;"C2,C1";"0603";2;"0.1uF";;;
2;"J3,J2";"JST04_1MM_RA";2;"QWIIC_RIGHT_ANGLE";;;
3;"LOGO2";"QWIIC_5MM";1;"QWIIC_LOGO_5MM";;;
4;"JP4,JP7,JP3,JP8";"STAND-OFF";4;"STAND-OFF";;;
5;"FRAME1";"CREATIVE_COMMONS";1;"FRAME-LETTER";;;
6;"U$35,U$3";"#SDA#0";2;"";;;
7;"R1,R2";"0603";2;"4.7k";;;
8;"D1";"LED-0603";1;"RED";;;
9;"LOGO1";"ORDERING_INSTRUCTIONS";1;"SPECIAL_INSTRUCTIONS-ORDERING";;;
10;"U$36,U$4";"#SCL#0";2;"";;;
11;"U$10,U$18";"SPARKX-SMALL";2;"SPARKX-LOGO3";;;
12;"U2";"SHTC3";1;"SHTC3";;;
13;"R5";"0603";1;"3.3k";;;
14;"R4";"0603";1;"10k";;;
15;"R3,R6";"0603";2;"1k";;;
16;"JP2,JP6,JP1,JP5";"FIDUCIAL-1X2";4;"FIDUCIAL1X2";;;
17;"U$33,U$1";"#GND#0";2;"";;;
18;"U$32";"#PWR#0";1;"";;;
19;"U$34,U$2";"#3#3V#0";2;"";;;
20;"U1";"STC31";1;"STC31";;;
21;"UNK0X2B0,UNK0X2C0,UNK0X2A0";"SMT-JUMPER_2_NO_SILK";3;"JUMPER-SMT_2_NO_SILK";;;
22;"U$7";"#0X2B#0";1;"";;;
23;"U$11";"STC310";1;"";;;
24;"U$13";"SHTC30";1;"";;;
25;"U$9";"#I�C#0";1;"";;;
26;"U$6";"#0X2A#0";1;"";;;
27;"U$5";"#LED#0";1;"";;;
28;"LOGO5";"OSHW-LOGO-S";1;"OSHW-LOGOS";;;
29;"U$12";"#0";1;"";;;
30;"J1";"1X04_NO_SILK";1;"";;;
31;"U$8";"#0X2C#0";1;"";;;
32;"U$14";"CO0";1;"";;;
33;"I2C0";"SMT-JUMPER_3_2-NC_TRACE_SILK";1;"JUMPER-SMT_3_2-NC_TRACE_SILK";;;
34;"U$15";"20";1;"";;;
35;"U$16";"SENSOR0";1;"";;;
36;"LED0";"SMT-JUMPER_2_NC_TRACE_SILK";1;"JUMPER-SMT_2_NC_TRACE_SILK";;;

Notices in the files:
parts and their libraries:
RELEASED UNDER THE CREATIVE COMMONS ATTRIBUTION SHARE-ALIKE 4.0 LICENSE
HTTPS://CREATIVECOMMONS.ORG/LICENSES/BY-SA/4.0
